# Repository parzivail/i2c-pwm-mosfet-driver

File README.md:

# I2C PWM MOSFET Driver

Buy this board [on Tindie](www.tindie.com/products/parzivail/i2c-pwm-mosfet-driver-mk-1/)!

This PWM driver board uses a PCA9685 controlled over I2C to drive up to 16 high-current loads with PWM via N-channeo MOSFETs. Perfect for 12V or 24V LED strips.

- PCA9685 PWM controller with 12-bit PWM resolution
- 3.3V and 5V compliant VCC and I2C
- Terminal block for driver power, isolated from chip power (provided over I2C)
- 16 independently-controlled outputs with up to 30V 3A per channel, driven by AO3400A N-channel MOSFETs
- Supports up to 5A total across all channels
- Reverse polarity protection via HXY AOD413A P-channel MOSFET up to 8A at 10V
- Two STEMMA QT/QUIIC-compatible I2C headers for daisy chaining
- 6-bit address select broken out on solder pads
- Spring-loaded terminal blocks for driver output
- Pads on each channel for optional current limiting resistors (bypassed by default with a solder jumper)
- Pads for optional power supply smoothing capacitor
- Red power LED
- 10K Pull-ups to VCC on SDA and SCL
- Compatible with Adafruit's PCA9685 libraries for Arduino and CircuitPython

## Changes from Mk1 to Mk2

- Removed polarity protection P-channel MOSFET
- Increased trace widths on each channel
- Converted an entire internal layer to a +V_LED power path

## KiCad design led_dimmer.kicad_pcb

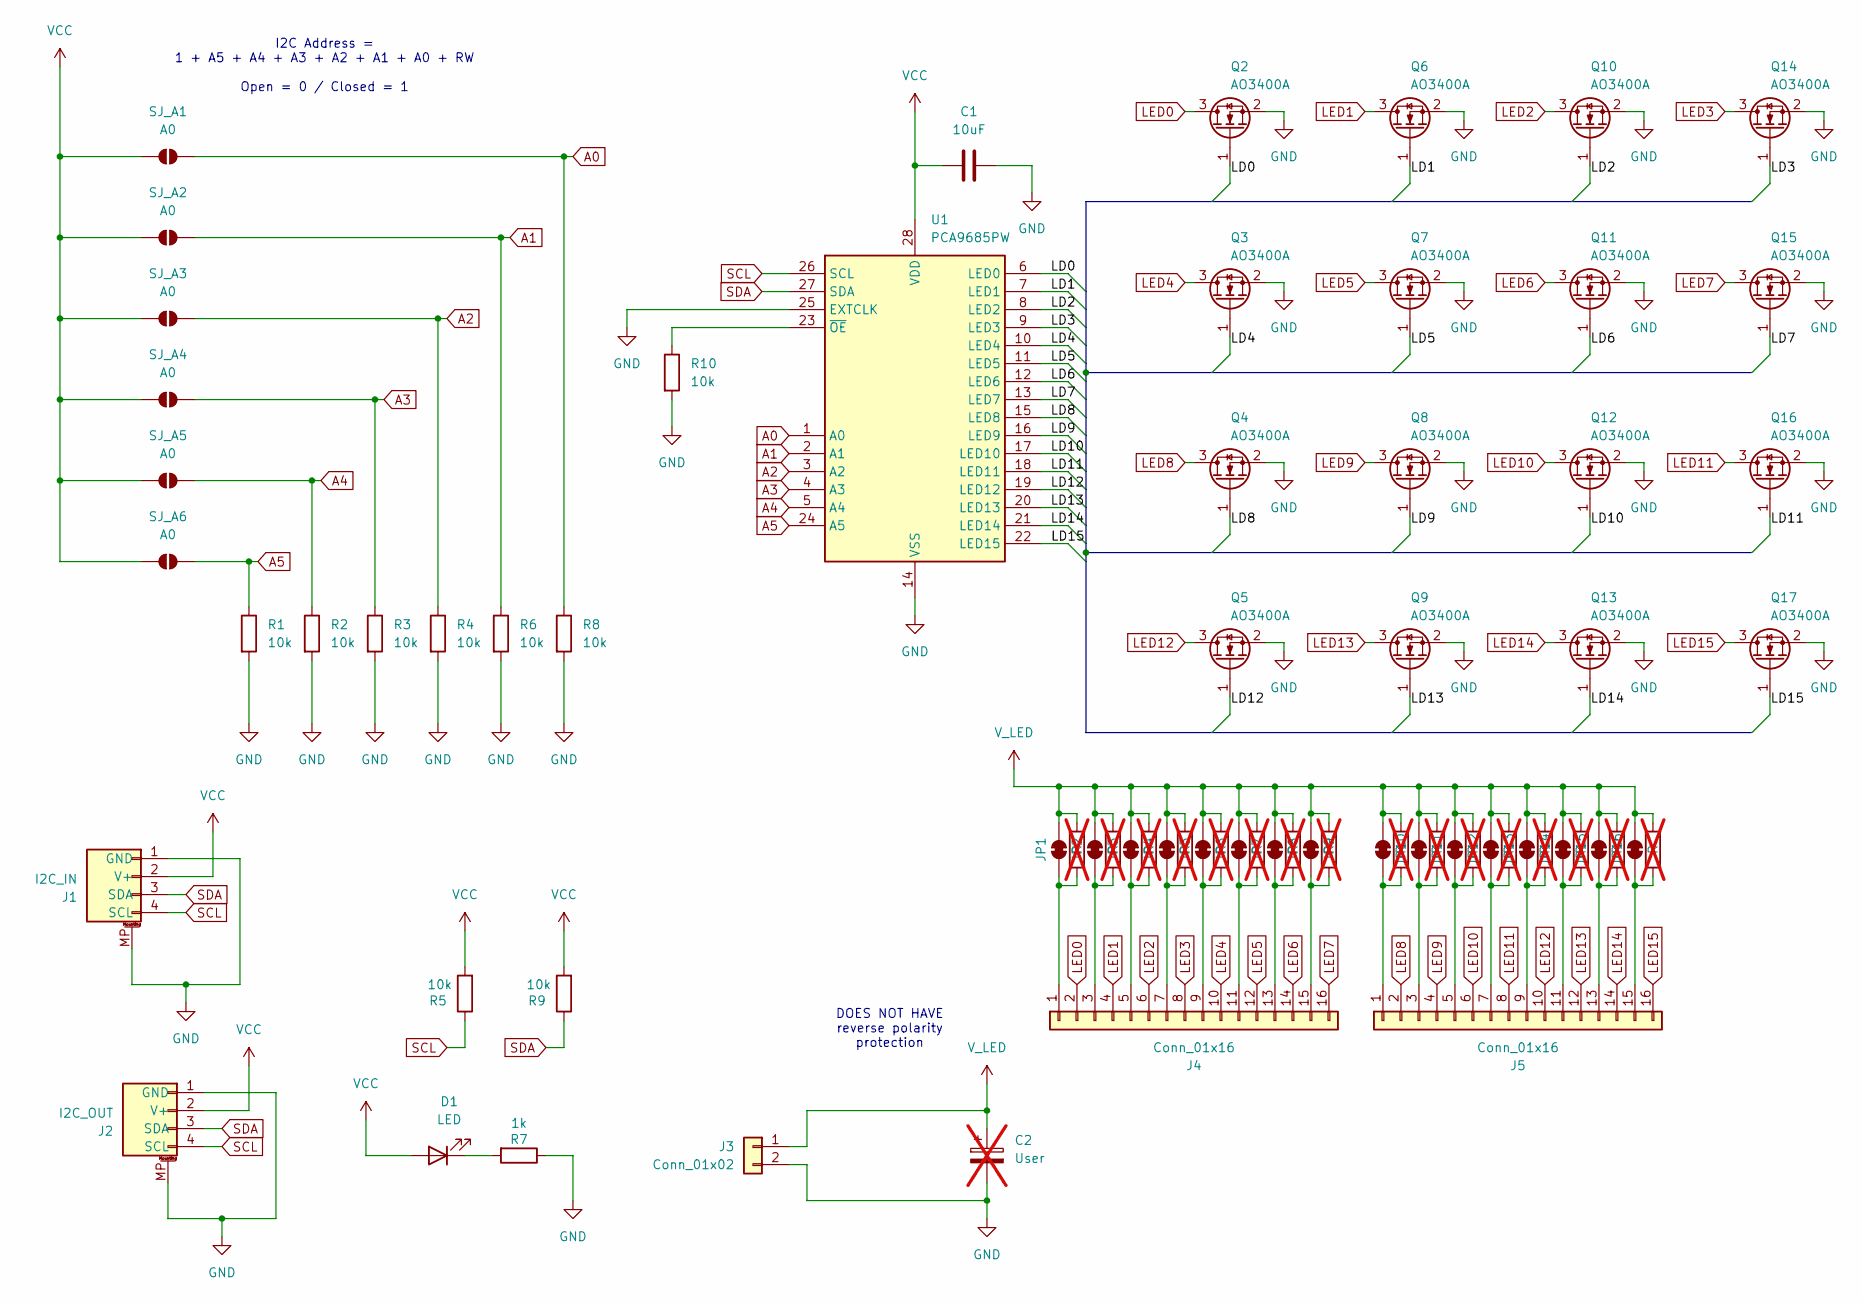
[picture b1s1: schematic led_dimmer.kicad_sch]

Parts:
C1: 10uF; C_0402_1005Metric; LCSC Part C15525
C2: User; CP_Radial_D8.0mm_P3.50mm; not fitted
D1: LED; LED_0603_1608Metric; LCSC Part C2286
J1: I2C_IN; JST_SH_SM04B-SRSS-TB_1x04-1MP_P1.00mm_Horizontal; LCSC Part C160404
J2: I2C_OUT; JST_SH_SM04B-SRSS-TB_1x04-1MP_P1.00mm_Horizontal; LCSC Part C160404
J3: Conn_01x02; TerminalBlock_Phoenix_MKDS-1,5-2_1x02_P5.00mm_Horizontal; LCSC Part C8404
J4, J5: Conn_01x16; CONN-TH_KF250T-5.0-2X8P; LCSC Part C976542
JP1, JP2, JP3, JP4, JP5, JP6, JP7, JP8, JP9, JP10, JP11, JP12, JP13, JP14, JP15, JP16: SolderJumper_2_Bridged; HighCurrentJumper
Q2, Q3, Q4, Q5, Q6, Q7, Q8, Q9, Q10, Q11, Q12, Q13, Q14, Q15, Q16, Q17: AO3400A; SOT-23; LCSC Part C20917
R1, R2, R3, R4, R5, R6, R8, R9, R10: 10k; R_0402_1005Metric; LCSC Part C25744
R7: 1k; R_0402_1005Metric; LCSC Part C11702
R11, R12, R13, R14, R15, R16, R17, R18, R19, R20, R21, R22, R23, R24, R25, R26: R; R_Axial_DIN0309_L9.0mm_D3.2mm_P12.70mm_Horizontal; not fitted
SJ_A1, SJ_A2, SJ_A3, SJ_A4, SJ_A5, SJ_A6: A0; SolderJumper-2_P1.3mm_Open_TrianglePad1.0x1.5mm
U1: PCA9685PW; TSSOP-28_4.4x9.7mm_P0.65mm; LCSC Part C2678753

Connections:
/LD0: Q2.1 (G), U1.6 (LED0)
/LD1: Q6.1 (G), U1.7 (LED1)
/LD2: Q10.1 (G), U1.8 (LED2)
/LD3: Q14.1 (G), U1.9 (LED3)
/LD4: Q3.1 (G), U1.10 (LED4)
/LD5: Q7.1 (G), U1.11 (LED5)
/LD6: Q11.1 (G), U1.12 (LED6)
/LD7: Q15.1 (G), U1.13 (LED7)
/LD8: Q4.1 (G), U1.15 (LED8)
/LD9: Q8.1 (G), U1.16 (LED9)
/LD10: Q12.1 (G), U1.17 (LED10)
/LD11: Q16.1 (G), U1.18 (LED11)
/LD12: Q5.1 (G), U1.19 (LED12)
/LD13: Q9.1 (G), U1.20 (LED13)
/LD14: Q13.1 (G), U1.21 (LED14)
/LD15: Q17.1 (G), U1.22 (LED15)
A0: R8.1, SJ_A1.2 (B), U1.1 (A0)
A1: R6.1, SJ_A2.2 (B), U1.2 (A1)
A2: R4.1, SJ_A3.2 (B), U1.3 (A2)
A3: R3.1, SJ_A4.2 (B), U1.4 (A3)
A4: R2.1, SJ_A5.2 (B), U1.5 (A4)
A5: R1.1, SJ_A6.2 (B), U1.24 (A5)
GND: C1.2, C2.2, J1.1 (GND), J1.MP, J2.1 (GND), J2.MP, J3.2, Q2.2 (S), Q3.2 (S), Q4.2 (S), Q5.2 (S), Q6.2 (S), Q7.2 (S), Q8.2 (S), Q9.2 (S), Q10.2 (S), Q11.2 (S), Q12.2 (S), Q13.2 (S), Q14.2 (S), Q15.2 (S), Q16.2 (S), Q17.2 (S), R1.2, R2.2, R3.2, R4.2, R6.2, R7.1, R8.2, R10.2, U1.14 (VSS), U1.25 (EXTCLK)
LED0: J4.2, Q2.3 (D)
LED1: J4.4, Q6.3 (D)
LED2: J4.6, Q10.3 (D)
LED3: J4.8, Q14.3 (D)
LED4: J4.10, Q3.3 (D)
LED5: J4.12, Q7.3 (D)
LED6: J4.14, Q11.3 (D)
LED7: J4.16, Q15.3 (D)
LED8: J5.2, Q4.3 (D)
LED9: J5.4, Q8.3 (D)
LED10: J5.6, Q12.3 (D)
LED11: J5.8, Q16.3 (D)
LED12: J5.10, Q5.3 (D)
LED13: J5.12, Q9.3 (D)
LED14: J5.14, Q13.3 (D)
LED15: J5.16, Q17.3 (D)
unnamed: D1.1 (K), R7.2
unnamed: J4.1, JP1.1 (A), R11.2
unnamed: J4.3, JP2.1 (A), R12.2
unnamed: J4.5, JP3.1 (A), R13.2
unnamed: J4.7, JP4.1 (A), R14.2
unnamed: J4.9, JP5.1 (A), R15.2
unnamed: J4.11, JP6.1 (A), R16.2
unnamed: J4.13, JP7.1 (A), R17.2
unnamed: J4.15, JP8.1 (A), R18.2
unnamed: J5.1, JP9.1 (A), R19.2
unnamed: J5.3, JP10.1 (A), R20.2
unnamed: J5.5, JP11.1 (A), R21.2
unnamed: J5.7, JP12.1 (A), R22.2
unnamed: J5.9, JP13.1 (A), R23.2
unnamed: J5.11, JP14.1 (A), R24.2
unnamed: J5.13, JP15.1 (A), R25.2
unnamed: J5.15, JP16.1 (A), R26.2
unnamed: R10.1, U1.23 (~OE)
SCL: J1.4 (SCL), J2.4 (SCL), R5.1, U1.26 (SCL)
SDA: J1.3 (SDA), J2.3 (SDA), R9.1, U1.27 (SDA)
VCC: C1.1, D1.2 (A), J1.2 (V+), J2.2 (V+), R5.2, R9.2, SJ_A1.1 (A), SJ_A2.1 (A), SJ_A3.1 (A), SJ_A4.1 (A), SJ_A5.1 (A), SJ_A6.1 (A), U1.28 (VDD)
V_LED: C2.1, J3.1, JP1.2 (B), JP2.2 (B), JP3.2 (B), JP4.2 (B), JP5.2 (B), JP6.2 (B), JP7.2 (B), JP8.2 (B), JP9.2 (B), JP10.2 (B), JP11.2 (B), JP12.2 (B), JP13.2 (B), JP14.2 (B), JP15.2 (B), JP16.2 (B), R11.1, R12.1, R13.1, R14.1, R15.1, R16.1, R17.1, R18.1, R19.1, R20.1, R21.1, R22.1, R23.1, R24.1, R25.1, R26.1

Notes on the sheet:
I2C Address = 1 + A5 + A4 + A3 + A2 + A1 + A0 + RW Open = 0 / Closed = 1
DOES NOT HAVE reverse polarity protection

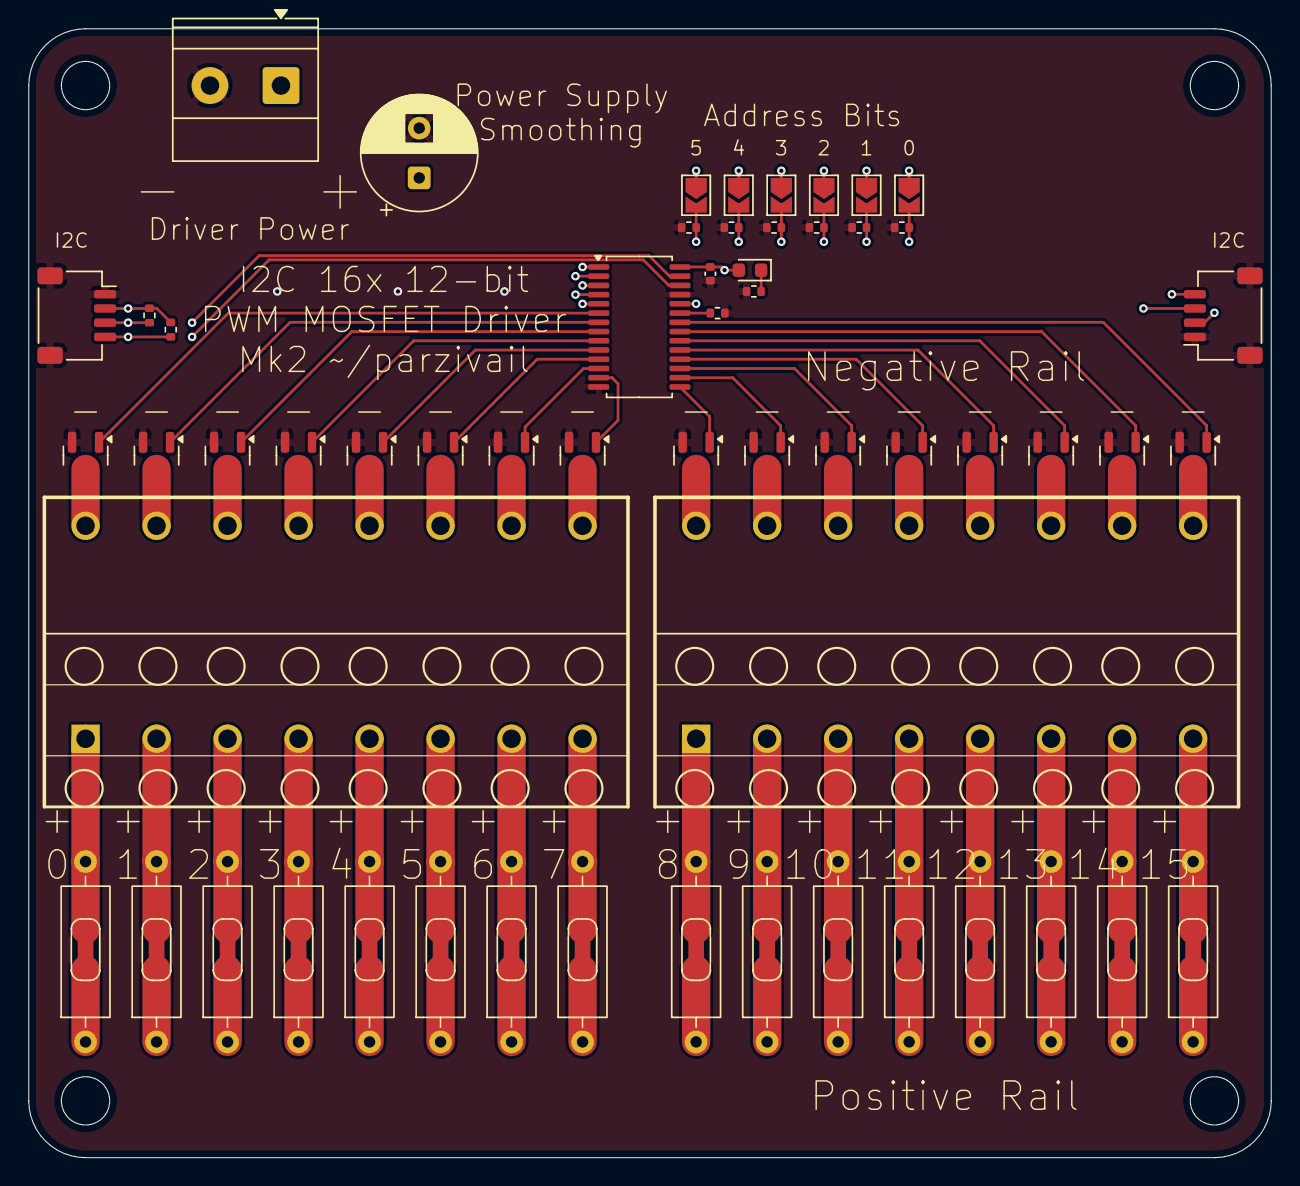
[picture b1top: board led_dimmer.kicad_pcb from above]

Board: 4 copper layers, 87.5 x 79.5 mm, 73 parts (0 on the bottom side), 61 nets.

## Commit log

2025-09-15 Create LICENSE
2025-09-15 Remove reverse polarity protection MOSFET
2025-09-15 README
